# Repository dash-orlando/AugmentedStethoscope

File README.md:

#thebeat
Sound analysis and playback

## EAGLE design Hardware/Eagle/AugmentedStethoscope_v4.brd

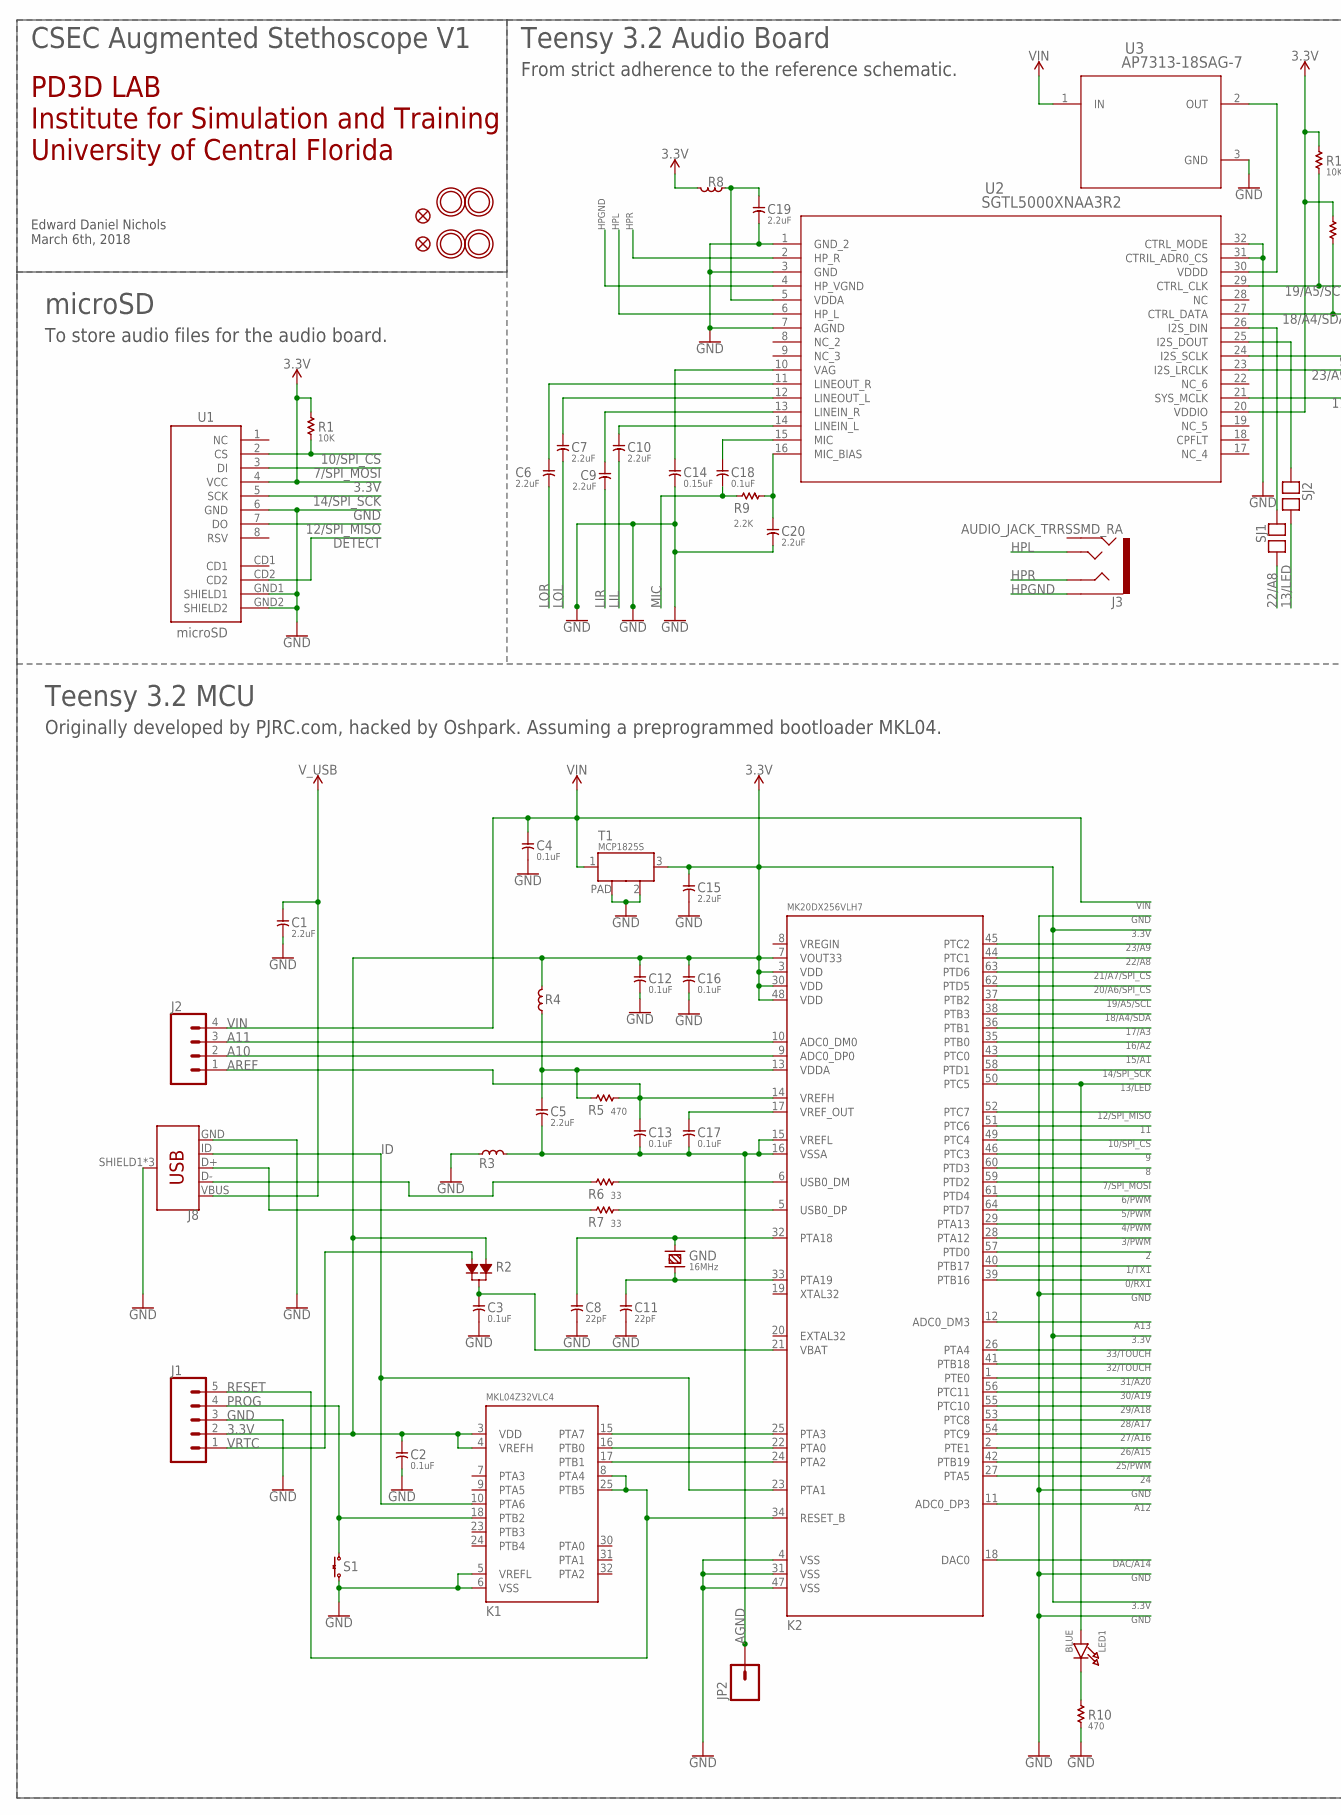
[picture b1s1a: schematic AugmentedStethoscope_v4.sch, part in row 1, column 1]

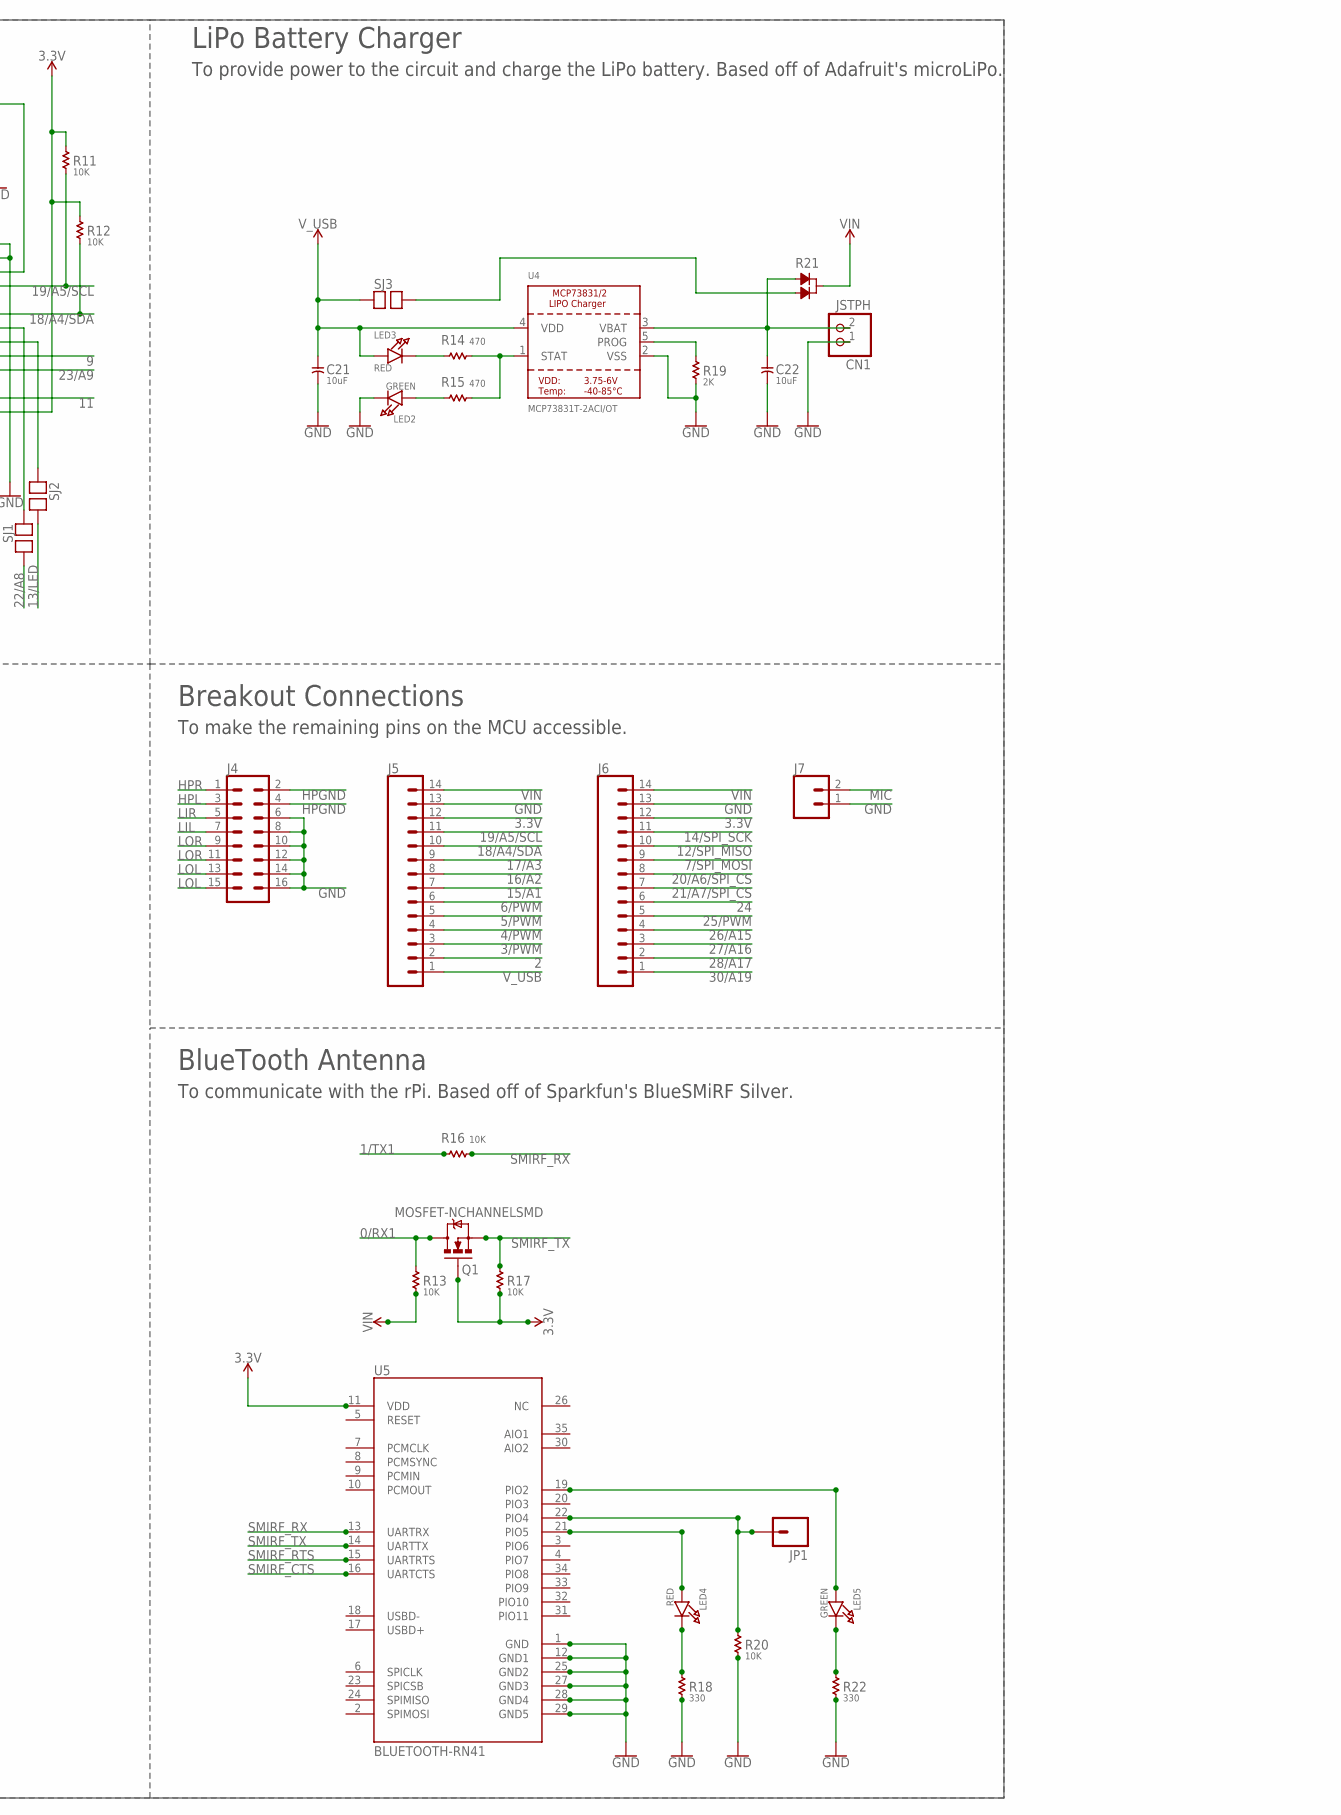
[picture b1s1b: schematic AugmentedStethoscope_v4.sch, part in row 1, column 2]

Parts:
C1, C5, C6, C7, C9, C10, C15, C19, C20: 2.2uF; C0805
C2, C3, C4, C12, C13, C16, C17: 0.1uF; C0603
C8, C11: 22pF; C0603
C14: 0.15uF; C0805
C18: 0.1uF; C0805
C21, C22: 10uF; C0603
CN1: JSTPH; JSTPH2
FID2, FID3: FIDUCIAL""; FIDUCIAL_1MM
GND: 16MHz; HC49US
J1: CONN_05; 1X05
J2: CONN_04; 1X04
J3: AUDIO_JACK_TRRSSMD_RA; AUDIO_JACK_3.5MM_TRRS_SMD_RA
J4: CONN_08X2; 2X8
J5, J6: CONN_14; 1X14
J7: CONN_02; 1X02
J8: USB_MICRO-B_FEMALE-SMT; USB-B-MICRO-SMD
JP1, JP2: M01SMDNS; 1X01NS
K1: MKL04Z32VLC4; LQFP32-08
K2: MK20DX256VLH7; LQFP64-05
LED1: BLUE; CHIPLED_0805
LED2, LED5: GREEN; CHIPLED_0805
LED3, LED4: RED; CHIPLED_0805
Q1: MOSFET-NCHANNELSMD; SOT23-3
R1, R11, R12, R13, R16, R17, R20: 10K; R0603
R2, R21: DIODE_DUAL; SOT-23
R3, R4, R8: FERRITE; L0603
R5, R10, R14, R15: 470; R0603
R6, R7: 33; R0603
R9: 2.2K; R0603
R18, R22: 330; R0603
R19: 2K; R0603
S1: TACT_SWITCH; ALPS_SKHH
SJ1, SJ2, SJ3: SOLDERJUMPER
T1: MCP1825S; SOT-223
U1: microSD; MICRO-SD-SOCKET-PP
U2: SGTL5000XNAA3R2; QFN32
U3: AP7313-18SAG-7; SOT-23
U4: MCP73831T-2ACI/OT; SOT23-5
U5: BLUETOOTH-RN41; RN41
U$1, U$15, U$17, U$18: MOUNTINGHOLE2.5; MOUNTINGHOLE_2.5_PLATED

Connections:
0/RX1: K2.39 (PTB16), Q1.3 (D), R13.2
1/TX1: K2.40 (PTB17), R16.1
2: J5.2, K2.57 (PTD0)
3.3V: C2.1, C12.1, C15.1, C16.1, J1.2, J5.12, J6.12, K1.3 (VDD), K1.4 (VREFH), K2.3 (VDD), K2.7 (VOUT33), K2.30 (VDD), K2.48 (VDD), Q1.1 (G), R1.2, R2.1, R4.2, R8.2, R11.2, R12.2, R17.1, T1.3 (OUT), U1.4 (VCC), U2.20 (VDDIO), U5.11 (VDD)
3/PWM: J5.3, K2.28 (PTA12)
4/PWM: J5.4, K2.29 (PTA13)
5/PWM: J5.5, K2.64 (PTD7)
6/PWM: J5.6, K2.61 (PTD4)
7/SPI_MOSI: J6.9, K2.59 (PTD2), U1.3 (DI)
8: K2.60 (PTD3)
9: K2.46 (PTC3), U2.24 (I2S_SCLK)
10/SPI_CS: K2.49 (PTC4), R1.1, U1.2 (CS)
11: K2.51 (PTC6), U2.21 (SYS_MCLK)
12/SPI_MISO: J6.10, K2.52 (PTC7), U1.7 (DO)
13/LED: K2.50 (PTC5), LED1.A, SJ2.2
14/SPI_SCK: J6.11, K2.58 (PTD1), U1.5 (SCK)
15/A1: J5.7, K2.43 (PTC0)
16/A2: J5.8, K2.35 (PTB0)
17/A3: J5.9, K2.36 (PTB1)
18/A4/SDA: J5.10, K2.38 (PTB3), R12.1, U2.27 (CTRL_DATA)
19/A5/SCL: J5.11, K2.37 (PTB2), R11.1, U2.29 (CTRL_CLK)
20/A6/SPI_CS: J6.8, K2.62 (PTD5)
21/A7/SPI_CS: J6.7, K2.63 (PTD6)
22/A8: K2.44 (PTC1), SJ1.2
23/A9: K2.45 (PTC2), U2.23 (I2S_LRCLK)
24: J6.6, K2.27 (PTA5)
25/PWM: J6.5, K2.42 (PTB19)
26/A15: J6.4, K2.2 (PTE1)
27/A16: J6.3, K2.54 (PTC9)
28/A17: J6.2, K2.53 (PTC8)
29/A18: K2.55 (PTC10)
30/A19: J6.1, K2.56 (PTC11)
31/A20: K2.1 (PTE0)
32/TOUCH: K2.41 (PTB18)
33/TOUCH: K2.26 (PTA4)
A10: J2.2, K2.9 (ADC0_DP0)
A11: J2.3, K2.10 (ADC0_DM0)
A12: K2.11 (ADC0_DP3)
A13: K2.12 (ADC0_DM3)
AGND: C5.2, C13.2, C17.2, JP2.1, K2.15 (VREFL), K2.16 (VSSA), R3.2
AREF: C13.1, J2.1, K2.14 (VREFH), R5.2
D3: LED4.C, R18.2
D4: LED5.C, R22.2
D+: J8.D+, R7.1
D-: J8.D-, R6.1
DAC/A14: K2.18 (DAC0)
DETECT: U1.CD2
GND: C1.2, C2.2, C3.2, C4.2, C8.2, C11.2, C12.2, C14.2, C15.2, C16.2, C19.2, C20.2, C21.2, C22.2, CN1.1, J1.3, J4.6, J4.8, J4.10, J4.12, J4.14, J4.16, J5.13, J6.13, J7.1, J8.GND, J8.SHIELD1 (SHIELD), J8.SHIELD2 (SHIELD), J8.SHIELD3 (SHIELD), K1.5 (VREFL), K1.6 (VSS), K2.4 (VSS), K2.31 (VSS), K2.47 (VSS), LED2.C, R3.1, R10.1, R18.1, R19.1, R20.1, R22.1, S1.3, S1.4 (3), T1.2 (GND), T1.PAD, U1.6 (GND), U1.GND1 (SHIELD1), U1.GND2 (SHIELD2), U2.1 (GND_2), U2.3 (GND), U2.7 (AGND), U2.31 (CTRIL_ADR0_CS), U2.32 (CTRL_MODE), U3.3 (GND), U4.2 (VSS), U5.1 (GND), U5.12 (GND1), U5.25 (GND2), U5.27 (GND3), U5.28 (GND4), U5.29 (GND5)
HPGND: J3.EARTH, J4.2, J4.4, U2.4 (HP_VGND)
HPL: J3.TIP, J4.3, U2.6 (HP_L)
HPR: J3.RING1, J4.1, U2.2 (HP_R)
ID: J8.ID, K1.10 (PTA6), K2.23 (PTA1)
LIL: C10.2, J4.7
LIL_ISO: C10.1, U2.14 (LINEIN_L)
LIR: C9.2, J4.5
LIR_ISO: C9.1, U2.13 (LINEIN_R)
LOL: C7.2, J4.13, J4.15
LOL_ISO: C7.1, U2.12 (LINEOUT_L)
LOR: C6.2, J4.9, J4.11
LOR_ISO: C6.1, U2.11 (LINEOUT_R)
MIC: C18.2, J7.2, R9.1
MIC_BIAS: C20.1, R9.2, U2.16 (MIC_BIAS)
unnamed: C22.1, CN1.2, R21.1, U4.3 (VBAT)
unnamed: K1.16 (PTB0), K2.22 (PTA0)
unnamed: K1.17 (PTB1), K2.24 (PTA2)
unnamed: C14.1, U2.10 (VAG)
unnamed: C8.1, GND.1, K2.32 (PTA18)
unnamed: C11.1, GND.2, K2.33 (PTA19)
unnamed: SJ1.1, U2.26 (I2S_DIN)
unnamed: K2.5 (USB0_DP), R7.2
unnamed: C17.1, K2.17 (VREF_OUT)
unnamed: U2.30 (VDDD), U3.2 (OUT)
unnamed: SJ2.1, U2.25 (I2S_DOUT)
unnamed: K2.6 (USB0_DM), R6.2
unnamed: C5.1, K2.13 (VDDA), R4.1, R5.1
unnamed: R21.2, SJ3.2
unnamed: LED1.C, R10.2
unnamed: C3.1, K2.21 (VBAT), R2.3
unnamed: K1.15 (PTA7), K2.25 (PTA3)
unnamed: LED3.C, R14.1
unnamed: R14.2, R15.2, U4.1 (STAT)
unnamed: LED4.A, U5.21 (PIO5)
unnamed: LED5.A, U5.19 (PIO2)
unnamed: R19.2, U4.5 (PROG)
unnamed: LED2.A, R15.1
unnamed: C19.1, R8.1, U2.5 (VDDA)
unnamed: C18.1, U2.15 (MIC)
PIO4: JP1.1, R20.2, U5.22 (PIO4)
PROG: J1.4, K1.18 (PTB2), S1.1, S1.2 (1)
RESET: J1.5, K1.8 (PTA4), K1.25 (PTB5), K2.34 (RESET_B)
SMIRF_CTS: U5.16 (UARTCTS)
SMIRF_RTS: U5.15 (UARTRTS)
SMIRF_RX: R16.2, U5.13 (UARTRX)
SMIRF_TX: Q1.2 (S), R17.2, U5.14 (UARTTX)
VIN: C4.1, J2.4, J5.14, J6.14, R13.1, R21.3, T1.1 (IN), U3.1 (IN)
VRTC: J1.1, R2.2
V_USB: C1.1, C21.1, J5.1, J8.VBUS, LED3.A, SJ3.1, U4.4 (VDD)

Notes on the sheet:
Teensy 3.2 MCU
Originally developed by PJRC.com, hacked by Oshpark. Assuming a preprogrammed bootloader MKL04.
microSD
To store audio files for the audio board.
Breakout Connections
To make the remaining pins on the MCU accessible.
BlueTooth Antenna
To communicate with the rPi. Based off of Sparkfun's BlueSMiRF Silver.
Teensy 3.2 Audio Board
From strict adherence to the reference schematic.
LiPo Battery Charger
To provide power to the circuit and charge the LiPo battery. Based off of Adafruit's microLiPo.
PD3D LAB Institute for Simulation and Training University of Central Florida
CSEC Augmented Stethoscope V1
Edward Daniel Nichols March 6th, 2018

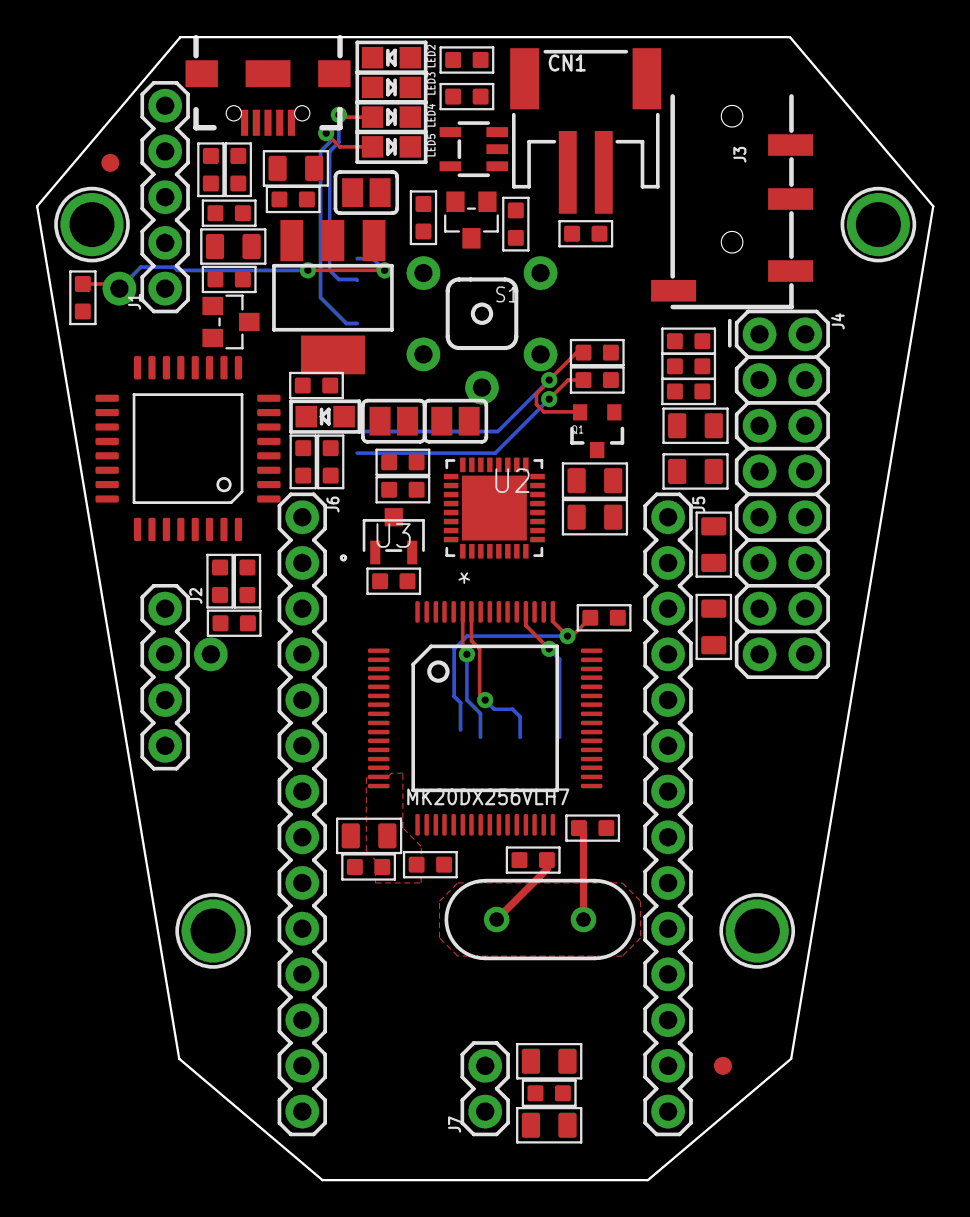
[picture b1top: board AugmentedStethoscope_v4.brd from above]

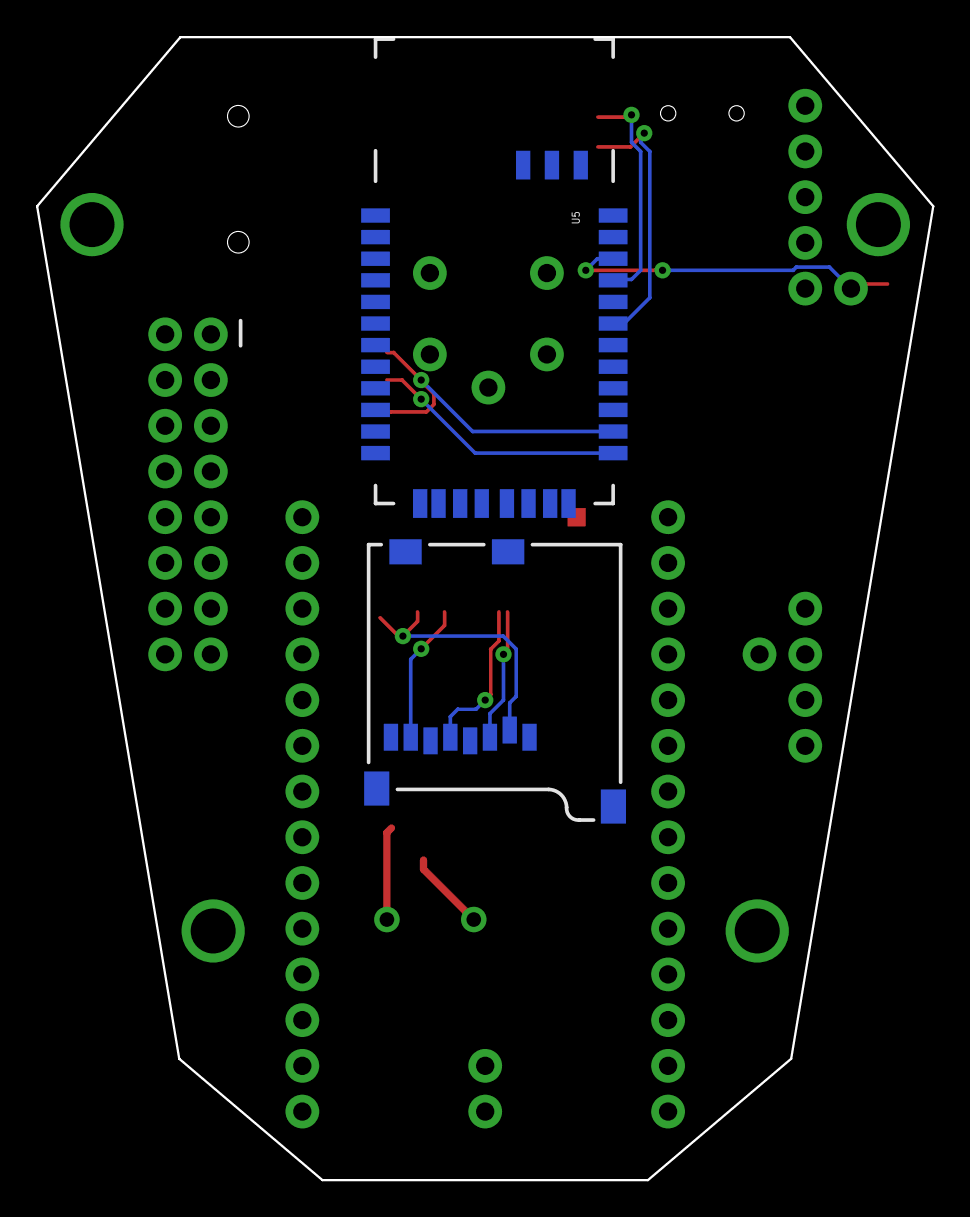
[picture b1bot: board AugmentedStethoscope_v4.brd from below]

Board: 2 copper layers, 49.8 x 63.5 mm, 80 parts (2 on the bottom side), 86 nets.

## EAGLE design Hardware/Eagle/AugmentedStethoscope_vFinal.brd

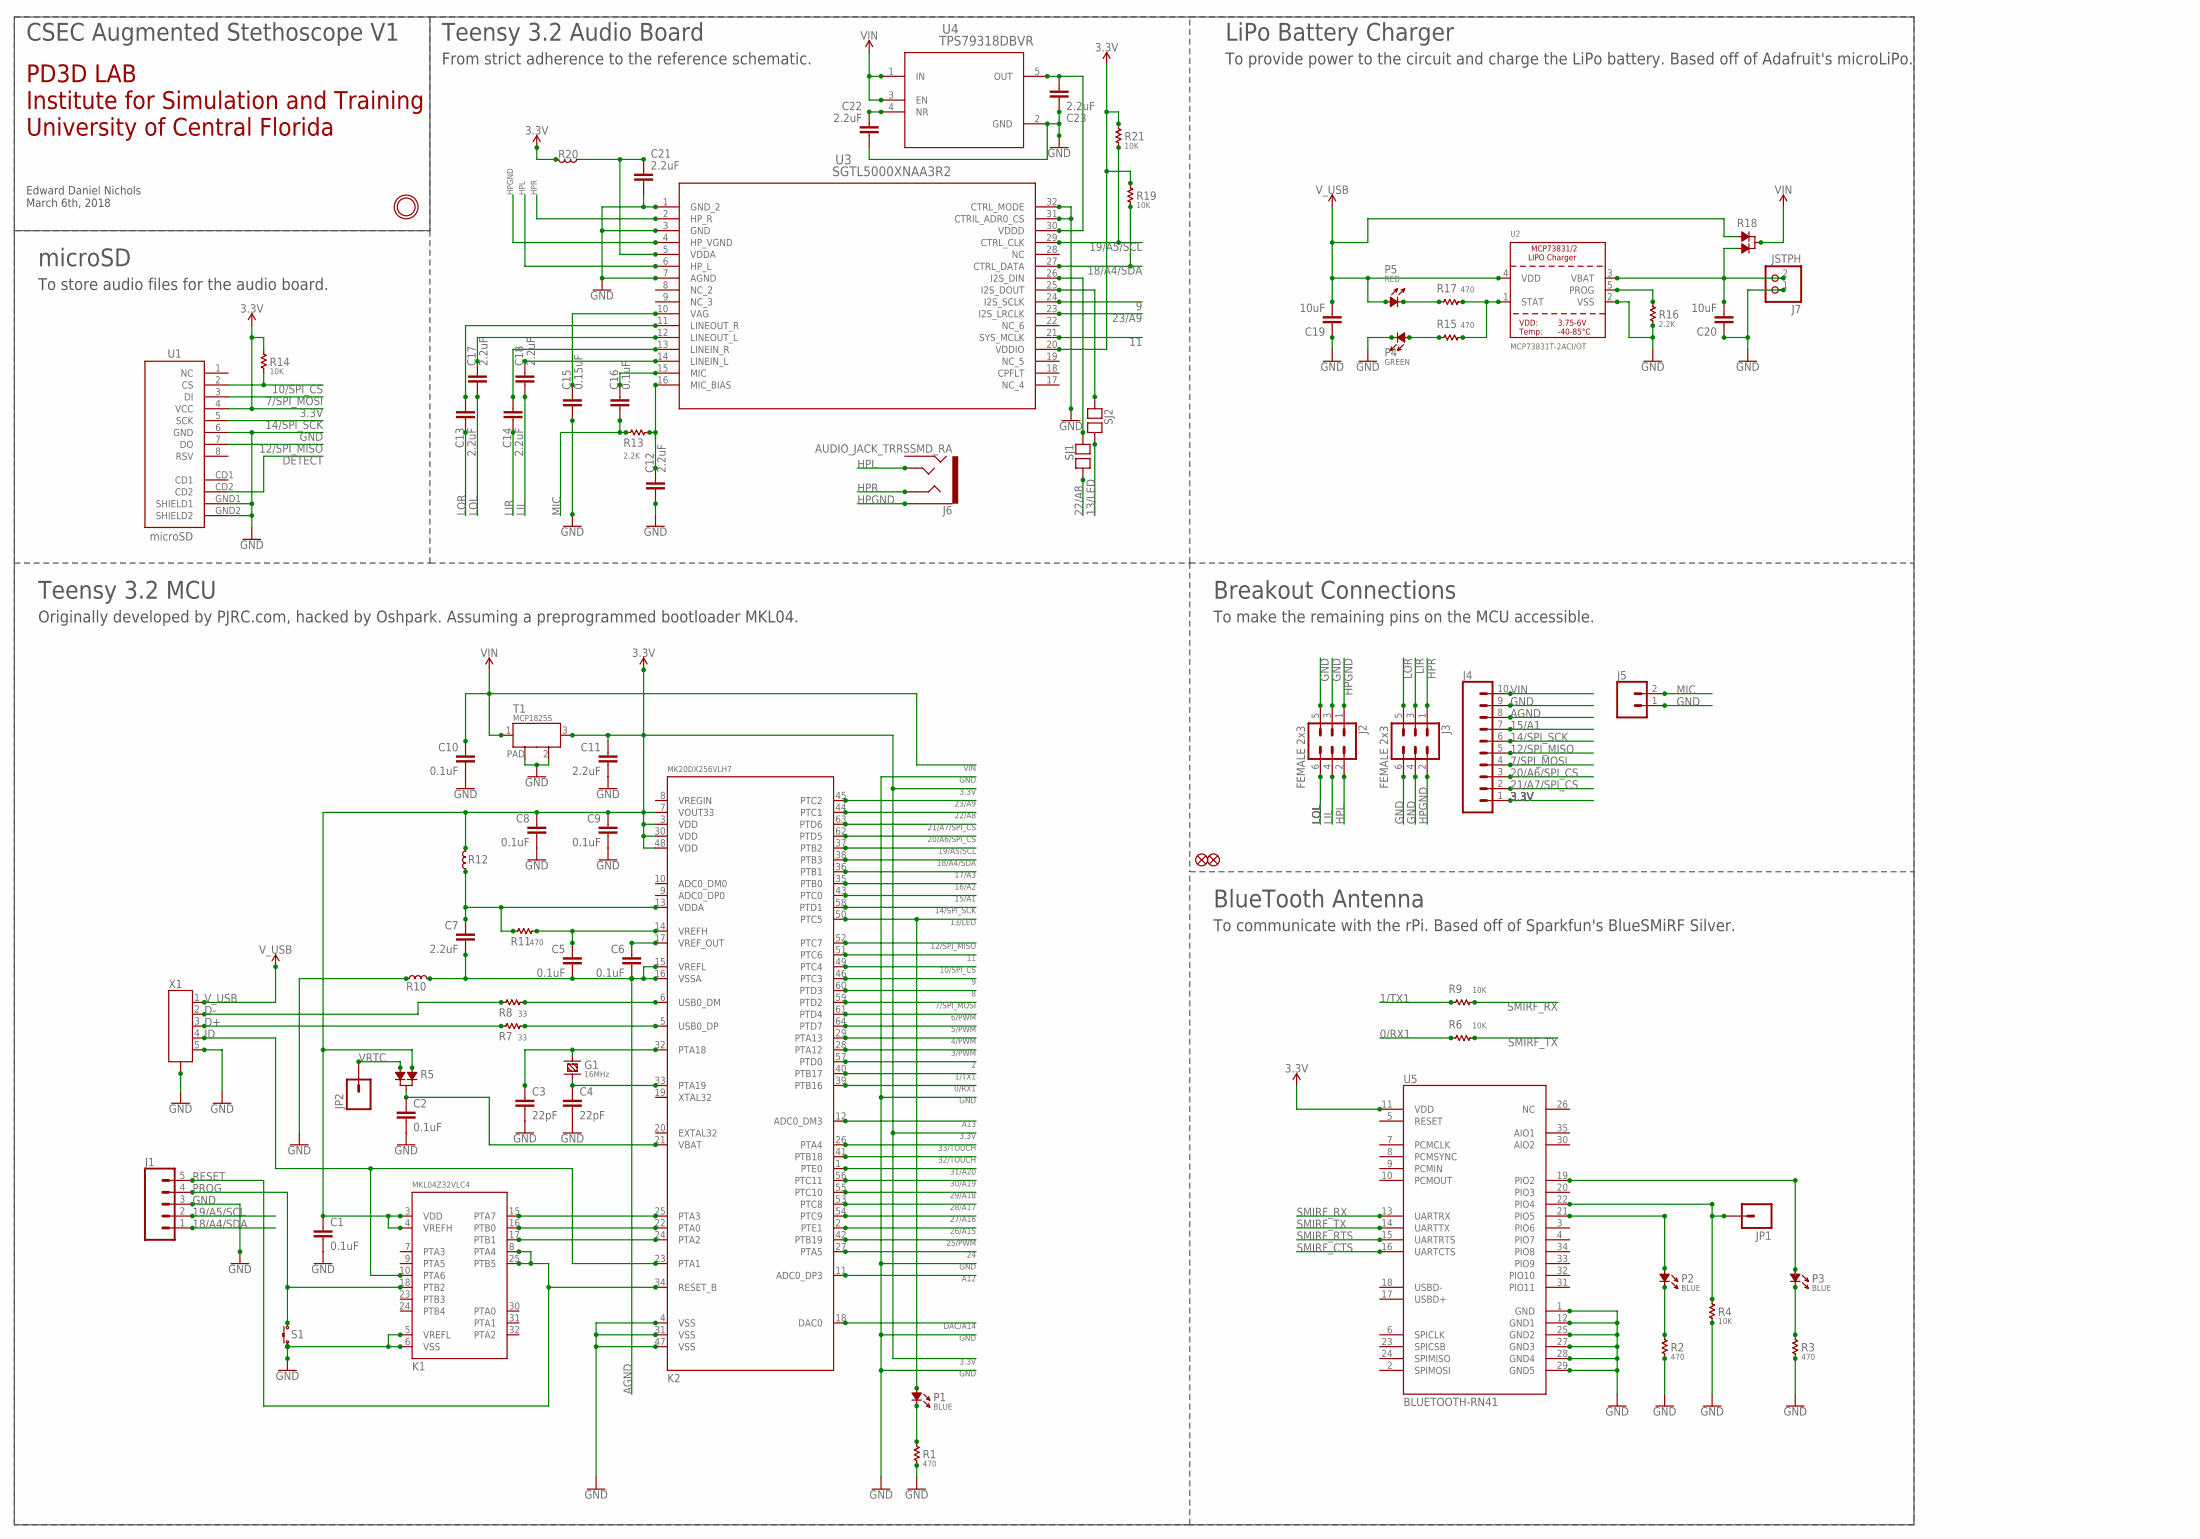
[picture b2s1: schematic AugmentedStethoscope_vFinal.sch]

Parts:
C1, C2, C5, C6, C8, C9, C10, C16: 0.1uF; 0603
C3, C4: 22pF; 0603
C7, C11, C12, C13, C14, C17, C18, C21, C22, C23: 2.2uF; 0603
C15: 0.15uF; 0603
C19, C20: 10uF; 0805
FID1, FID2: FIDUCIAL""; FIDUCIAL_1MM
G1: 16MHz; HC49US
J1: CONN_05; 1X05
J2, J3: FEMALE 2x3; 2X3
J4: CONN_10"; 1X10
J5: CONN_02; 1X02
J6: AUDIO_JACK_TRRSSMD_RA; AUDIO_JACK_3.5MM_TRRS_SMD_RA
J7: JSTPH; JSTPH2
JP1, JP2: M01SMDNS; 1X01NS
K1: MKL04Z32VLC4; LQFP32-08
K2: MK20DX256VLH7; LQFP64-05
P1, P2, P3: BLUE; LED-0805
P4: GREEN; LED-0805
P5: RED; LED-0805
R1, R2, R3, R11, R15, R17: 470; R0603
R4, R6, R9, R14, R19, R21: 10K; R0603
R5, R18: DIODE_DUAL; SOT-23
R7, R8: 33; R0603
R10, R12, R20: FERRITE; L0603
R13, R16: 2.2K; R0603
S1: TACT_SWITCH; ALPS_SKHH
SJ1, SJ2: SOLDERJUMPER
T1: MCP1825S; SOT-223
U1: microSD; MICRO-SD-SOCKET-PP
U2: MCP73831T-2ACI/OT; SOT23-5
U3: SGTL5000XNAA3R2; QFN32
U4: TPS79318DBVR; DBV5
U5: BLUETOOTH-RN41; RN41
U$1: MOUNTINGHOLE2.5; MOUNTINGHOLE_2.5_PLATED
X1: MINI-USB; MOLEX_SD-67503-010

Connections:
0/RX1: K2.39 (PTB16), R6.1
1/TX1: K2.40 (PTB17), R9.1
2: K2.57 (PTD0)
3.3V: C1.1, C8.1, C9.1, C11.1, J4.1, K1.3 (VDD), K1.4 (VREFH), K2.3 (VDD), K2.7 (VOUT33), K2.30 (VDD), K2.48 (VDD), R5.1, R12.2, R14.2, R19.2, R20.2, R21.2, T1.3 (OUT), U1.4 (VCC), U3.20 (VDDIO), U5.11 (VDD)
3/PWM: K2.28 (PTA12)
4/PWM: K2.29 (PTA13)
5/PWM: K2.64 (PTD7)
6/PWM: K2.61 (PTD4)
7/SPI_MOSI: J4.4, K2.59 (PTD2), U1.3 (DI)
8: K2.60 (PTD3)
9: K2.46 (PTC3), U3.24 (I2S_SCLK)
10/SPI_CS: K2.49 (PTC4), R14.1, U1.2 (CS)
11: K2.51 (PTC6), U3.21 (SYS_MCLK)
12/SPI_MISO: J4.5, K2.52 (PTC7), U1.7 (DO)
13/LED: K2.50 (PTC5), P1.+, SJ2.2
14/SPI_SCK: J4.6, K2.58 (PTD1), U1.5 (SCK)
15/A1: J4.7, K2.43 (PTC0)
16/A2: K2.35 (PTB0)
17/A3: K2.36 (PTB1)
18/A4/SDA: J1.1, K2.38 (PTB3), R19.1, U3.27 (CTRL_DATA)
19/A5/SCL: J1.2, K2.37 (PTB2), R21.1, U3.29 (CTRL_CLK)
20/A6/SPI_CS: J4.3, K2.62 (PTD5)
21/A7/SPI_CS: J4.2, K2.63 (PTD6)
22/A8: K2.44 (PTC1), SJ1.2
23/A9: K2.45 (PTC2), U3.23 (I2S_LRCLK)
24: K2.27 (PTA5)
25/PWM: K2.42 (PTB19)
26/A15: K2.2 (PTE1)
27/A16: K2.54 (PTC9)
28/A17: K2.53 (PTC8)
29/A18: K2.55 (PTC10)
30/A19: K2.56 (PTC11)
31/A20: K2.1 (PTE0)
32/TOUCH: K2.41 (PTB18)
33/TOUCH: K2.26 (PTA4)
A12: K2.11 (ADC0_DP3)
A13: K2.12 (ADC0_DM3)
AGND: C5.2, C6.2, C7.2, J4.8, K2.15 (VREFL), K2.16 (VSSA), R10.2
D3: P2.-, R2.2
D4: P3.-, R3.2
D+: R7.1, X1.3
D-: R8.1, X1.2
DAC/A14: K2.18 (DAC0)
DETECT: U1.CD2
GND: C1.2, C2.2, C3.2, C4.2, C8.2, C9.2, C10.2, C11.2, C12.2, C15.1, C19.1, C20.1, C21.2, C22.2, C23.1, J1.3, J2.3, J2.5, J3.4, J3.6, J4.9, J5.1, J7.1, K1.5 (VREFL), K1.6 (VSS), K2.4 (VSS), K2.31 (VSS), K2.47 (VSS), P4.-, R1.1, R2.1, R3.1, R4.1, R10.1, R16.1, S1.3, S1.4 (3), T1.2 (GND), T1.PAD, U1.6 (GND), U1.GND1 (SHIELD1), U1.GND2 (SHIELD2), U2.2 (VSS), U3.1 (GND_2), U3.3 (GND), U3.7 (AGND), U3.31 (CTRIL_ADR0_CS), U3.32 (CTRL_MODE), U4.2 (GND), U5.1 (GND), U5.12 (GND1), U5.25 (GND2), U5.27 (GND3), U5.28 (GND4), U5.29 (GND5), X1.5, X1.P$1 (CASE), X1.P$2 (CASE), X1.P$3 (CASE), X1.P$4 (CASE), X1.P$5 (CASE), X1.P$6 (CASE)
HPGND: J2.1, J3.2, J6.EARTH, U3.4 (HP_VGND)
HPL: J2.2, J6.TIP, U3.6 (HP_L)
HPR: J3.1, J6.RING1, U3.2 (HP_R)
ID: K1.10 (PTA6), K2.23 (PTA1), X1.4
LIL: C18.2, J2.4
LIL_ISO: C18.1, U3.14 (LINEIN_L)
LIR: C14.2, J3.3
LIR_ISO: C14.1, U3.13 (LINEIN_R)
LOL: C17.2, J2.6
LOL_ISO: C17.1, U3.12 (LINEOUT_L)
LOR: C13.2, J3.5
LOR_ISO: C13.1, U3.11 (LINEOUT_R)
MIC: C16.1, J5.2, R13.1
MIC_BIAS: C12.1, R13.2, U3.16 (MIC_BIAS)
unnamed: C20.2, J7.2, R18.2, U2.3 (VBAT)
unnamed: K1.16 (PTB0), K2.22 (PTA0)
unnamed: K1.17 (PTB1), K2.24 (PTA2)
unnamed: C15.2, U3.10 (VAG)
unnamed: C3.1, G1.1, K2.32 (PTA18)
unnamed: C4.1, G1.2, K2.33 (PTA19)
unnamed: C5.1, K2.14 (VREFH), R11.2
unnamed: C22.1, U4.4 (NR)
unnamed: SJ1.1, U3.26 (I2S_DIN)
unnamed: K2.5 (USB0_DP), R7.2
unnamed: C6.1, K2.17 (VREF_OUT)
unnamed: C23.2, U3.30 (VDDD), U4.5 (OUT)
unnamed: SJ2.1, U3.25 (I2S_DOUT)
unnamed: K2.6 (USB0_DM), R8.2
unnamed: C16.2, U3.15 (MIC)
unnamed: P3.+, U5.19 (PIO2)
unnamed: C7.1, K2.13 (VDDA), R11.1, R12.1
unnamed: P1.-, R1.2
unnamed: C2.1, K2.21 (VBAT), R5.3
unnamed: K1.15 (PTA7), K2.25 (PTA3)
unnamed: P5.-, R17.1
unnamed: R15.2, R17.2, U2.1 (STAT)
unnamed: P2.+, U5.21 (PIO5)
unnamed: R16.2, U2.5 (PROG)
unnamed: P4.+, R15.1
unnamed: C21.1, R20.1, U3.5 (VDDA)
PIO4: JP1.1, R4.2, U5.22 (PIO4)
PROG: J1.4, K1.18 (PTB2), S1.1, S1.2 (1)
RESET: J1.5, K1.8 (PTA4), K1.25 (PTB5), K2.34 (RESET_B)
SMIRF_CTS: U5.16 (UARTCTS)
SMIRF_RTS: U5.15 (UARTRTS)
SMIRF_RX: R9.2, U5.13 (UARTRX)
SMIRF_TX: R6.2, U5.14 (UARTTX)
VIN: C10.1, J4.10, R18.3, T1.1 (IN), U4.1 (IN), U4.3 (EN)
VRTC: JP2.1, R5.2
V_USB: C19.2, P5.+, R18.1, U2.4 (VDD), X1.1

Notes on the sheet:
Teensy 3.2 MCU
Originally developed by PJRC.com, hacked by Oshpark. Assuming a preprogrammed bootloader MKL04.
microSD
To store audio files for the audio board.
Breakout Connections
To make the remaining pins on the MCU accessible.
BlueTooth Antenna
To communicate with the rPi. Based off of Sparkfun's BlueSMiRF Silver.
Teensy 3.2 Audio Board
From strict adherence to the reference schematic.
LiPo Battery Charger
To provide power to the circuit and charge the LiPo battery. Based off of Adafruit's microLiPo.
PD3D LAB Institute for Simulation and Training University of Central Florida
CSEC Augmented Stethoscope V1
Edward Daniel Nichols March 6th, 2018

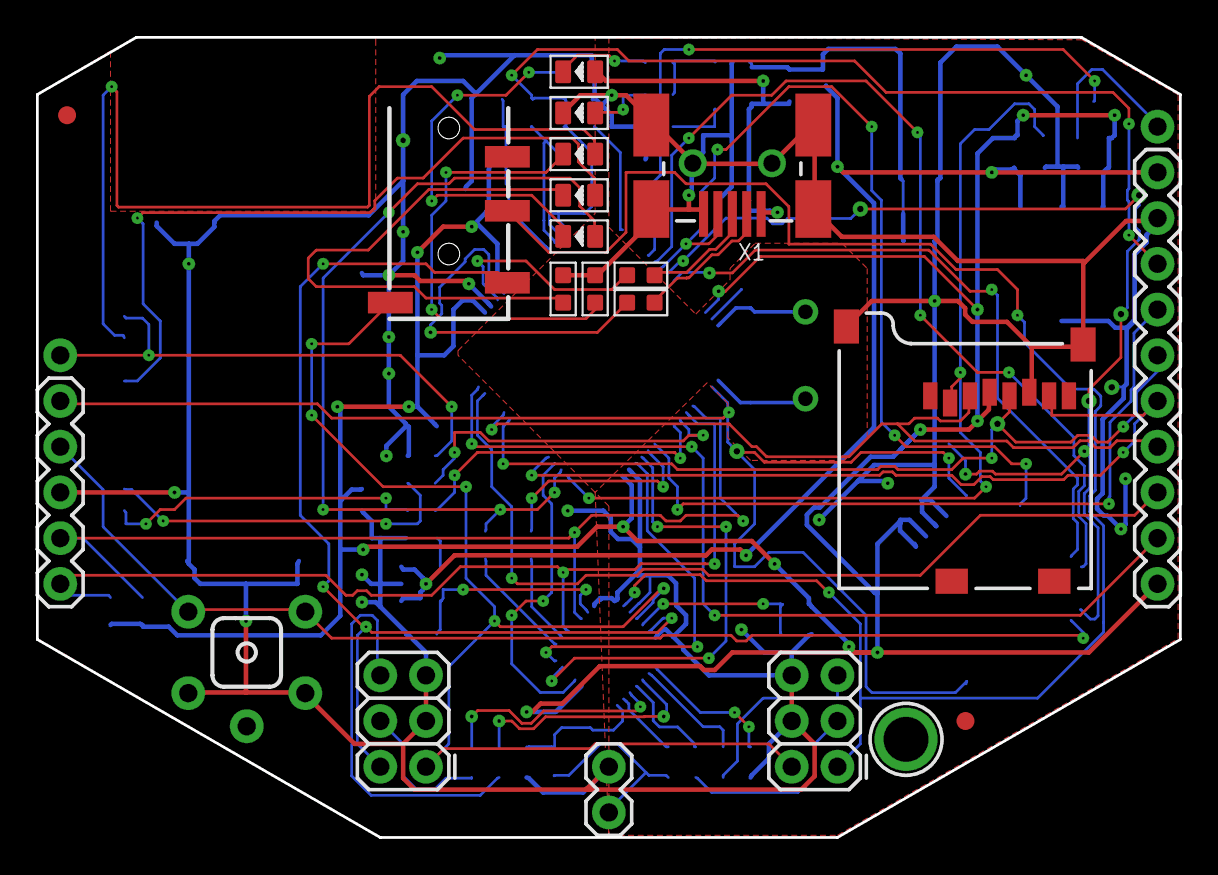
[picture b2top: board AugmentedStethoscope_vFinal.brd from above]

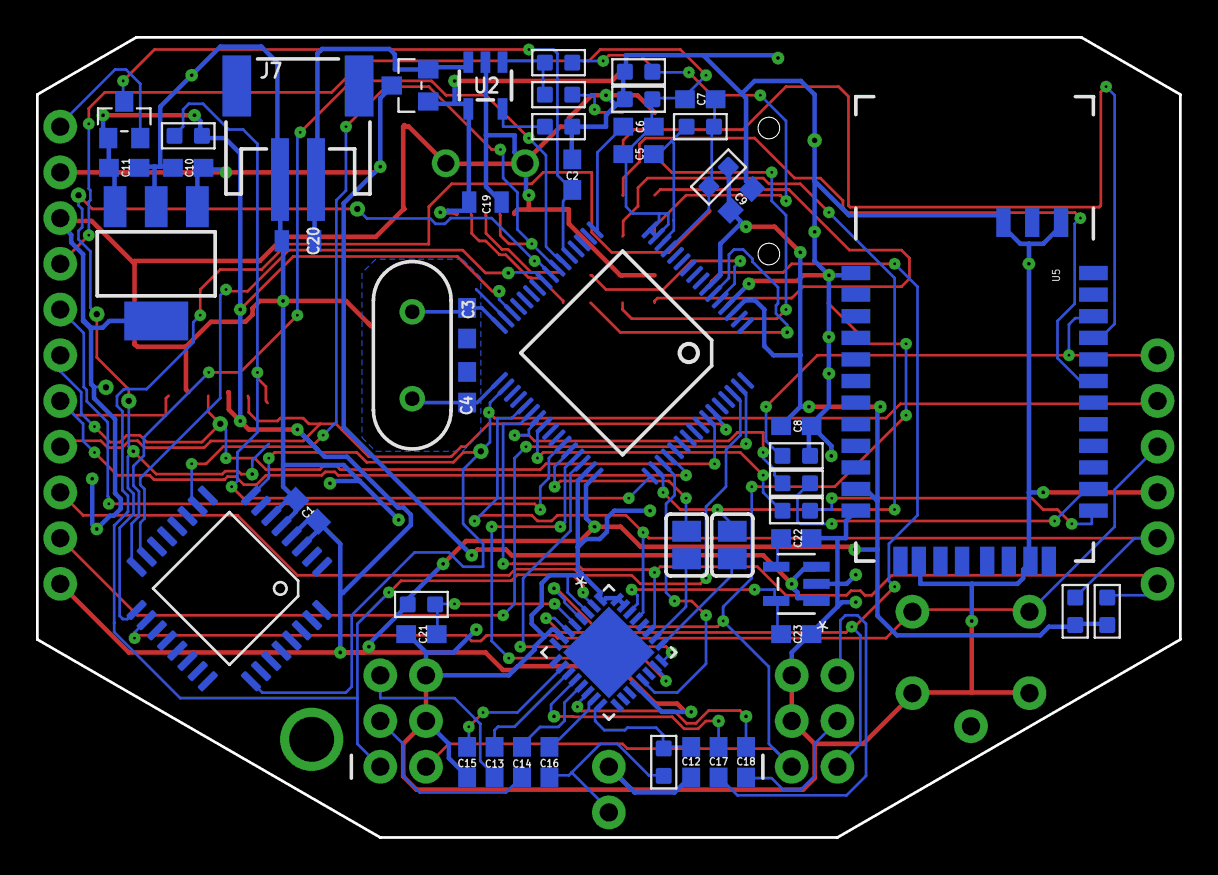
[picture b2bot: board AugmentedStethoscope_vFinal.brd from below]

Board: 2 copper layers, 63.5 x 44.5 mm, 74 parts (52 on the bottom side), 71 nets.

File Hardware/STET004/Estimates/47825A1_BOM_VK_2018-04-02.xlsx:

MOUSER
Part No. | Schematic ID | Type | Description | Package | Manufacturer | Manufacturer Part No. | Mouser Part No. | Unit Price | Quantity | Total Price | Reference
1 | C3, C4 | Capacitor | 22pF / 50VDC / C0G (NP0) | 603 | Murata Electronics | GCM1885C1H220FA16J | 81-GCM1885C1H220FA6J | 0.17 | 2 | 0.34 | https://www.mouser.com/datasheet/2/281/c03e-516224.pdf
2 | C1, C2, C5, C6, C8, C9, C10, C11, C16 | Capacitor | 0.1uF / 25VDC / X5R | 603 | Taiyo Yuden | GMK063BJ104KP-F | 963-GMK063BJ104KP-F | 0.14000000000000001 | 8 | 1.1200000000000001 | https://www.mouser.com/datasheet/2/396/mlcc02_e-1307760.pdf
3 | C15 | Capacitor | 0.15uF / 25VDC / X5R | 603 | Taiyo Yuden | TMK107BJ154KA-T | 963-TMK107BJ154KA-T | 0.25 | 1 | 0.25 | ^
4 | C7, C11, 12, C13, C14, C17, C18, C21, C22, C23 | Capacitor | 2.2uF / 25 VDC / X6S | 603 | Taiyo Yuden | TMK107BC6225KA-T | 963-TMK107BC6225KA-T | 0.32 | 10 | 3.2 | ^
5 | C19, C20 | Capacitor | 10uF / 25VDC / X5R | 805 | Taiyo Yuden | TMK212BBJ106KD-T | 963-TMK212BBJ106KD-T | 0.39 | 2 | 0.78 | ^
6 | X1 | Connector | MINI USB | 5PN | MOLEX | 675031020 | 538-67503-1020 | 0.65 | 1 | 0.65 | https://www.mouser.com/datasheet/2/276/0675031020_IO_CONNECT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
7 | G1 | Crystal | 16MHz / 18pF / 10ppm | HC-49US | ABRACON | ABL-16.000MHz-B1U | 815-ABL-16-B1U | 0.47 | 1 | 0.47 | https://www.mouser.com/datasheet/2/3/ABL-10083.pdf
8 | R5, R18 | Diode | Dual Schottky, Common | SOT-23 | Nexperia | BAT54C,215 | 771-BAT54C-T/R | 0.24 | 2 | 0.48 | https://www.mouser.com/datasheet/2/302/BAT54_SER-1149775.pdf
9 | R10, R12, R20 | Ferrite | 600R / 100MHz | 603 | Murata Electronics | BLM18AG601SN1D | 81-BLM11A601S | 0.1 | 3 | 0.3 | https://www.mouser.com/datasheet/2/281/c31e-794748.pdf
10 | P5 | LED | Red LED | 805 | Kingbright | APTD2012LSURCK | 604-APTD2012LSURCK | 0.33 | 1 | 0.33 | https://www.mouser.com/datasheet/2/216/APTD2012LSURCK-1101937.pdf
11 | P4 | LED | Green LED | 805 | Kingbright | APTD2012LZGCK | 604-APTD2012LZGCK | 0.68 | 1 | 0.68 | https://www.mouser.com/datasheet/2/216/APTD2012LZGCK-1101817.pdf
12 | P1, P2, P3 | LED | Blue LED | 805 | Kingbright | APTD2012LQBC/D | 604-APTD2012LQBCD | 0.46 | 3 | 1.38 | https://www.mouser.com/datasheet/2/216/APTD2012LQBC-D-1102003.pdf
13 | K2 | Microcontroller | MK20DX256VLH7 | LQFP-64 | NXP | MK20DX256VLH7 | 841-MK20DX256VLH7 | 7.1 | 1 | 7.1 | https://www.mouser.com/datasheet/2/302/K20P64M72SF1-1126422.pdf
14 | R7, R8 | Resistor | 33 / 1% / 0.25 W | 603 | Panasonic | ERJ-PA3F33R0V | 667-ERJ-PA3F33R0V | 1.23 | 2 | 2.46 | https://www.mouser.com/datasheet/2/315/AOA0000C331-1141874.pdf
15 | R1, R2, R3, R4, R11, R15, R17 | Resistor | 470 / 0.5% / 0.25 W | 603 | Panasonic | ERJ-PA3D4700V | 667-ERJ-PA3D4700V | 0.37 | 7 | 2.59 | ^
16 | R13, R16 | Resistor | 2.2K / 0.5% / 0.25W | 603 | Panasonic | ERJ-PA3D2201V | 667-ERJ-PA3D2201V | 0.37 | 2 | 0.74 | ^
17 | R6, R9, R14, R19, R21 | Resistor | 10K / 0.5 % / 0.25W | 603 | Panasonic | ERJ-PA3D1002V | 667-ERJ-PA3D1002V | 0.37 | 5 | 1.85 | ^
18 | S1 | Tactile Switch | SPST | 6x6x5 MM | ALPS | SKHHPKA010 | 688-SKHHPK | 0.31 | 1 | 0.31 | http://www.alps.com/prod/info/E/PDF/Tact/SnapIn/SKHH/SKHHPKA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
19 | U2 | LIPO Charger | Battery Management Controller | SOT-23-5 | Microchip Technology | MCP73831T-2ACI/OT | 579-MCP73831T-2ACIOT | 0.68 | 1 | 0.68 | https://www.mouser.com/datasheet/2/268/20001984g-846362.pdf
20 | U3 | Audio Codec | Audio Codex Interface | QFN-32 | NXP | SGTL5000XNAA3R2 | 841-SGTL5000XNAA3R2 | 2.82 | 1 | 2.82 | https://www.mouser.com/datasheet/2/302/SGTL5000-1127744.pdf
21 | U4 | Voltage Regulator | 1.8V 200mA | SOT-23-5 | Texas Instruments | TPS79318DBVR | 595-TPS79318DBVR | 0.73 | 1 | 0.73 | http://www.ti.com/lit/gpn/tps793
22 | T1 | Voltage Regulator | 3.3V 500mA | SOT-223-3 | Microchip Technology | MCP1825S-3302E/DB | 579-MCP1825S-3302EDB | 0.62 | 1 | 0.62 | https://www.mouser.com/datasheet/2/268/22056b-475378.pdf
MOUSER ELECTRONICS TOTAL: |  |  |  |  |  |  |  |  | 57 | 29.88
SPARKFUN
Part No. | Schematic ID | Type | Description | Package | Manufacturer | Manufacturer Part No. | SparkFun Product No. | Unit Price | Quantity | Total Price | Reference:
23 | U1 | Connector | MicroSD Transflash Socket | SPI uSD SMD/SMT | 4UCON Technology Inc | 15882 T-FLASH-CON | PRT-00127 | 3.95 | 1 | 3.95 | https://www.sparkfun.com/products/127
24 | J6 | Connector | 3.5mm Audio Jack TRSS | 3.5MM TRSS SMD/SMT | 4UCON Technology Inc | 20153 TRSS-CON | PRT-12639 | 0.95 | 1 | 0.95 | https://www.sparkfun.com/products/12639
25 | J7 | Connector | JST Right Angle Connector | JST 2-Pin SMD/SMT | 4UCON Technology Inc | 17311 JSTPH-CON | PRT-08612 | 0.95 | 1 | 0.95 | https://www.sparkfun.com/products/8612
SPARKFUN TOTAL: |  |  |  |  |  |  |  |  | 3 | 5.85
PJRC
Part No. | Schematic ID | Type | Description | Package | Manufacturer | Manufacturer Part No. |  | Unit Price | Quantity | Total Price | Reference:
26 | K1 | Bootloader | MKL04Z32VLC4 (Preprogrammed) | LQFP-32 | PJRC | IC_MKL04Z32_TQFP32 |  | 6.95 | 1 | 6.95 | https://www.pjrc.com/store/ic_mkl02.html
PJRC TOTAL: |  |  |  |  |  |  |  |  | 1 | 6.95
COMPONENTS TOTAL: |  |  |  |  |  |  |  |  | 61 | 42.68

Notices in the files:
parts and their libraries:
SparkFun-Connectors: Licensing: Creative Commons ShareAlike 4.0 International - https://creativecommons.org/licenses/by-sa/4.0
microbuilder: This work is placed in the public domain, and may be freely used for commercial and non-commercial work with the following conditions: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
